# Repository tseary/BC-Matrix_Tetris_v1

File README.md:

# BC-Matrix_Tetris_v1
An Arduino tetris game for the Boldport Club Matrix

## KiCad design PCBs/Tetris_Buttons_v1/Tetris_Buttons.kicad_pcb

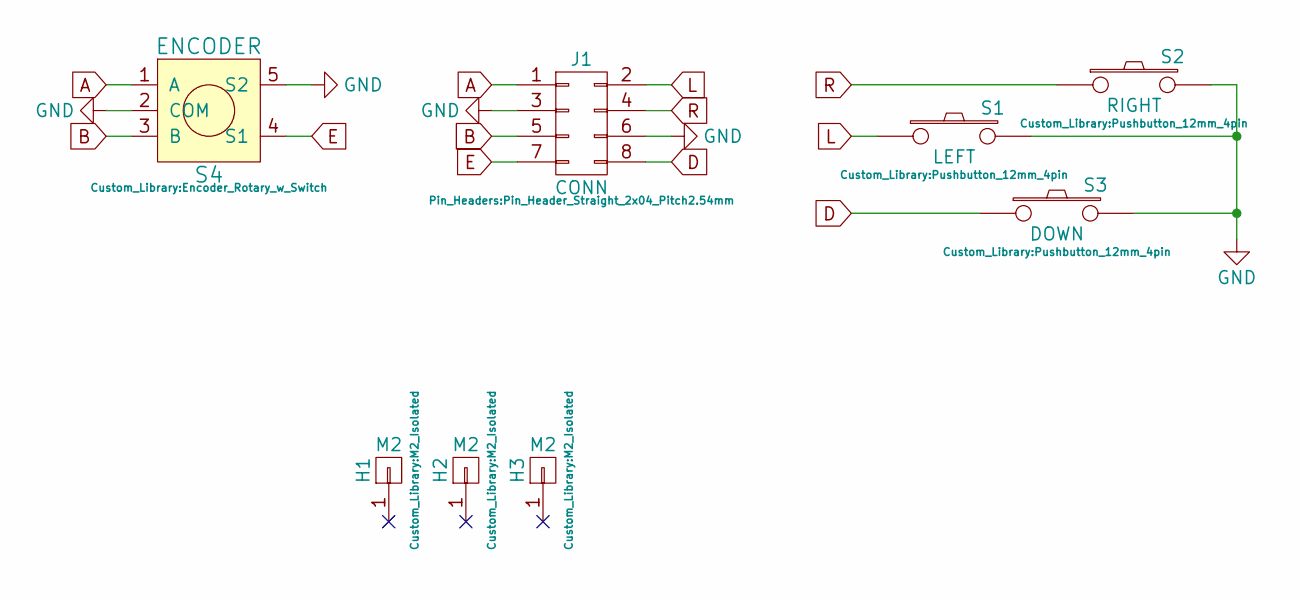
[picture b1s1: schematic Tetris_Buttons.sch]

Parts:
H1, H2, H3: M2; M2_Isolated
J1: CONN; Pin_Header_Straight_2x04_Pitch2.54mm
S1: LEFT; Pushbutton_12mm_4pin
S2: RIGHT; Pushbutton_12mm_4pin
S3: DOWN; Pushbutton_12mm_4pin
S4: ENCODER; Encoder_Rotary_w_Switch

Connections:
A: J1.1, S4.1 (A)
B: J1.5, S4.3 (B)
D: J1.8, S3.1
E: J1.7, S4.4 (S1)
GND: J1.3, J1.6, S1.2, S2.2, S3.2, S4.2 (COM), S4.5 (S2)
L: J1.2, S1.1
R: J1.4, S2.1

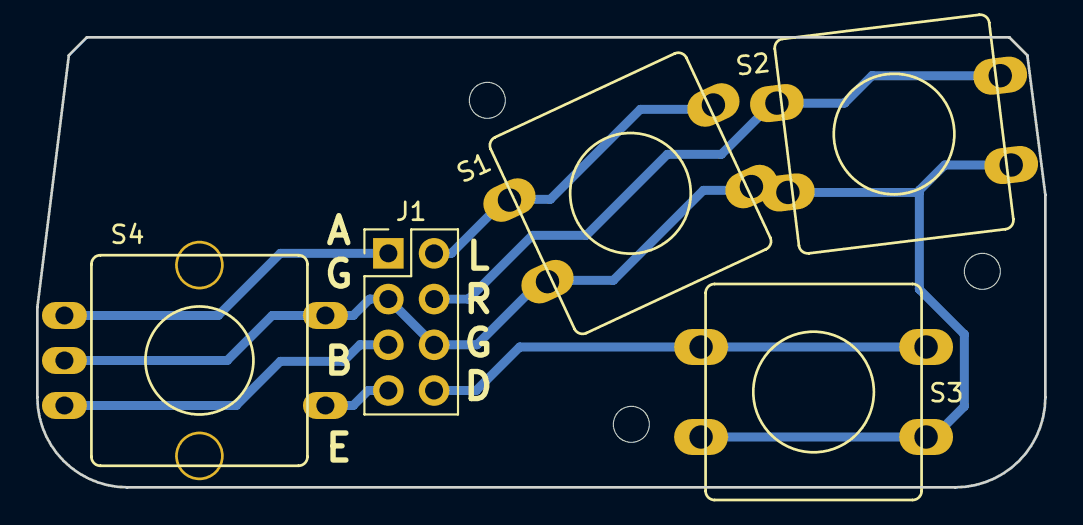
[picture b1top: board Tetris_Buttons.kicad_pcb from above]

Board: 2 copper layers, 56.0 x 25.0 mm, 8 parts (0 on the bottom side), 7 nets.

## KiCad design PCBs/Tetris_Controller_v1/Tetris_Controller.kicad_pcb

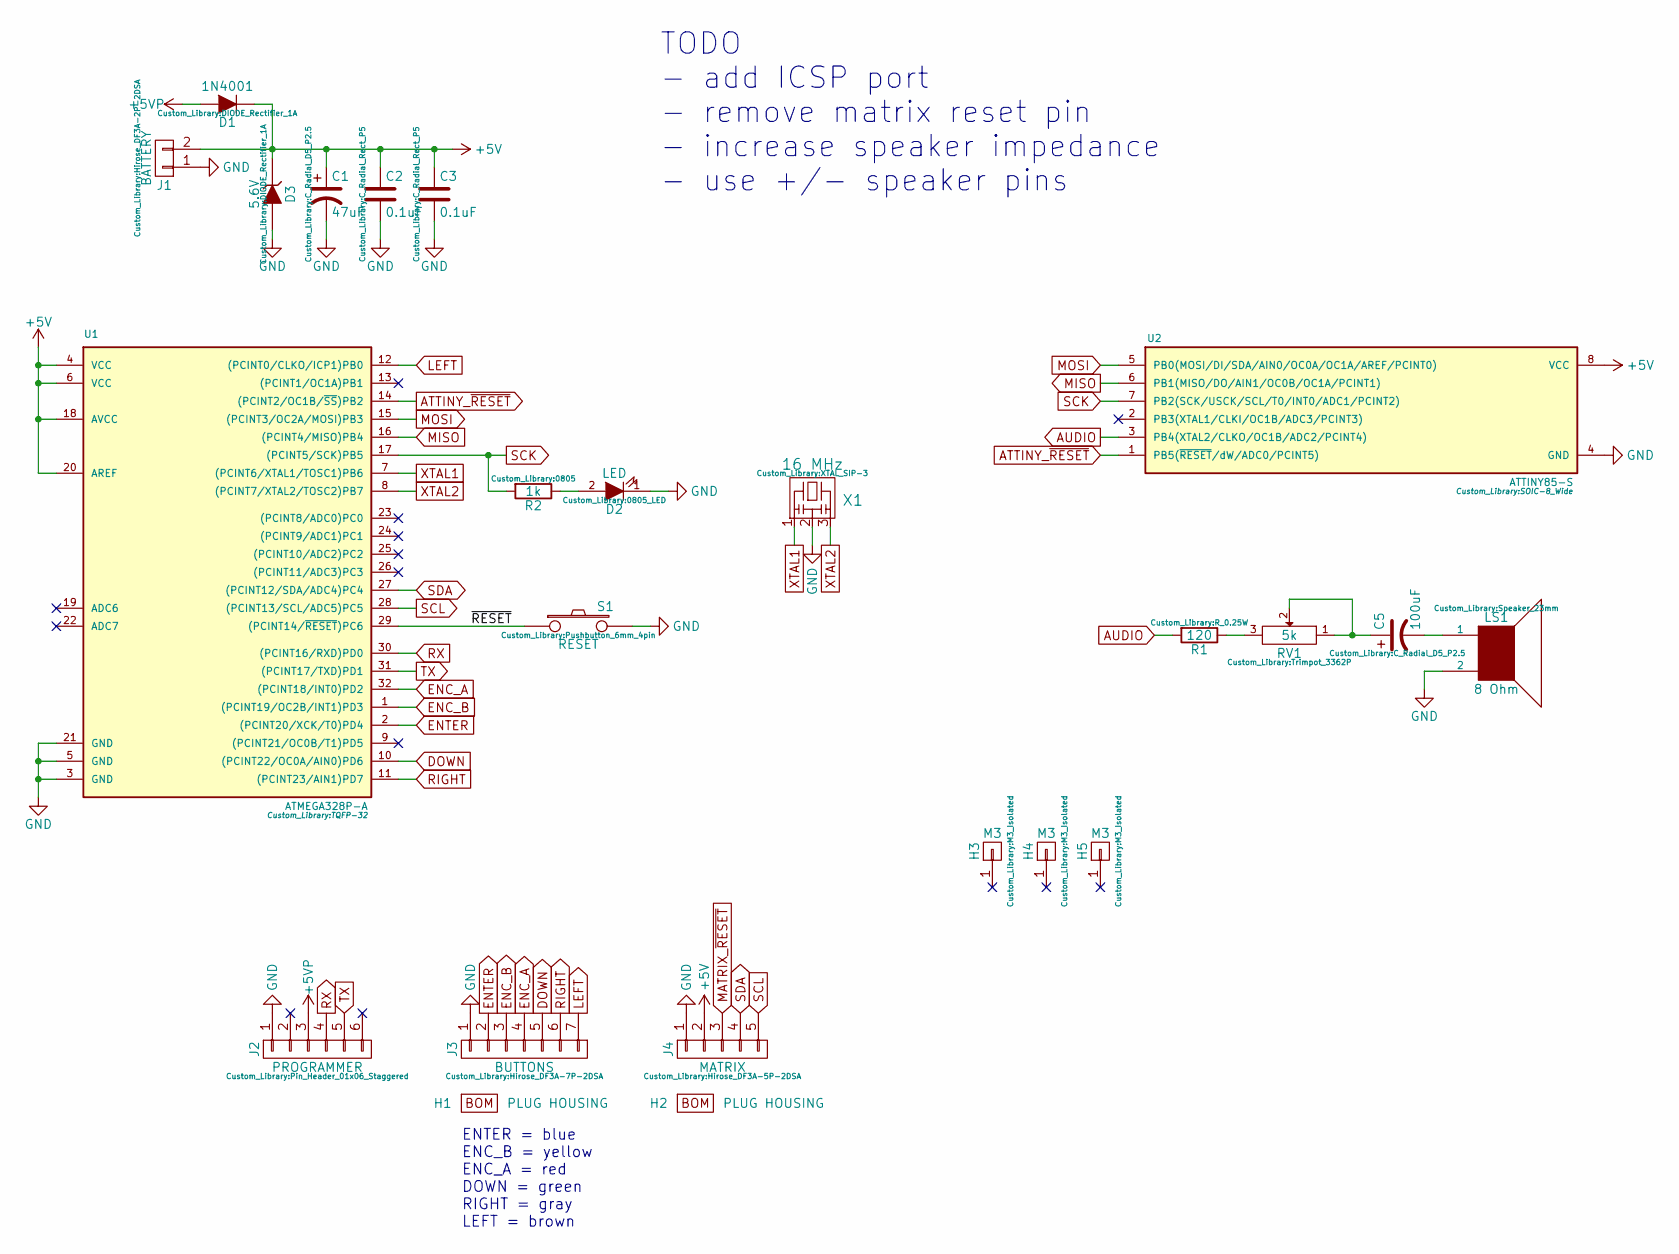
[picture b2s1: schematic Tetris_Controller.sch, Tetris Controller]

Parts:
C1: 47uF; C_Radial_D5_P2.5
C2, C3: 0.1uF; C_Radial_Rect_P5
C5: 100uF; C_Radial_D5_P2.5
D1: 1N4001; DIODE_Rectifier_1A
D2: LED; 0805_LED
D3: 5.6V; DIODE_Rectifier_1A
H1, H2: PLUG HOUSING
H3, H4, H5: M3; M3_Isolated
J1: BATTERY; Hirose_DF3A-2P-2DSA
J2: PROGRAMMER; Pin_Header_01x06_Staggered
J3: BUTTONS; Hirose_DF3A-7P-2DSA
J4: MATRIX; Hirose_DF3A-5P-2DSA
LS1: 8 Ohm; Speaker_23mm
R1: 120; R_0.25W
R2: 1k; 0805
RV1: 5k; Trimpot_3362P
S1: RESET; Pushbutton_6mm_4pin
U1: ATMEGA328P-A; TQFP-32
U2: ATTINY85-S; SOIC-8_Wide
X1: 16 MHz; XTAL_SIP-3

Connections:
+5V: C1.1, C2.1, C3.1, D1.1 (K), D3.1 (K), J1.2, J4.2, U1.4 (VCC), U1.6 (VCC), U1.18 (AVCC), U1.20 (AREF), U2.8 (VCC)
+5VP: D1.2 (A), J2.3
/~RESET: S1.1, U1.29 ((PCINT14/~RESET~)PC6)
ATTINY_~RESET: U1.14 ((PCINT2/OC1B/~SS~)PB2), U2.1 (PB5(~RESET~/dW/ADC0/PCINT5))
AUDIO: R1.2, U2.3 (PB4(XTAL2/CLKO/OC1B/ADC2/PCINT4))
DOWN: J3.5, U1.10 ((PCINT22/OC0A/AIN0)PD6)
ENC_A: J3.4, U1.32 ((PCINT18/INT0)PD2)
ENC_B: J3.3, U1.1 ((PCINT19/OC2B/INT1)PD3)
ENTER: J3.2, U1.2 ((PCINT20/XCK/T0)PD4)
GND: C1.2, C2.2, C3.2, D2.1 (K), D3.2 (A), J1.1, J2.1, J3.1, J4.1, LS1.2, S1.2, U1.3 (GND), U1.5 (GND), U1.21 (GND), U2.4 (GND), X1.2
LEFT: J3.7, U1.12 ((PCINT0/CLKO/ICP1)PB0)
MATRIX_~RESET: J4.3
MISO: U1.16 ((PCINT4/MISO)PB4), U2.6 (PB1(MISO/DO/AIN1/OC0B/OC1A/PCINT1))
MOSI: U1.15 ((PCINT3/OC2A/MOSI)PB3), U2.5 (PB0(MOSI/DI/SDA/AIN0/OC0A/OC1A/AREF/PCI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)
unnamed: C5.1, RV1.1, RV1.2
unnamed: C5.2, LS1.1
unnamed: D2.2 (A), R2.1
unnamed: R1.1, RV1.3
RIGHT: J3.6, U1.11 ((PCINT23/AIN1)PD7)
RX: J2.4, U1.30 ((PCINT16/RXD)PD0)
SCK: R2.2, U1.17 ((PCINT5/SCK)PB5), U2.7 (PB2(SCK/USCK/SCL/T0/INT0/ADC1/PCINT2))
SCL: J4.5, U1.28 ((PCINT13/SCL/ADC5)PC5)
SDA: J4.4, U1.27 ((PCINT12/SDA/ADC4)PC4)
TX: J2.5, U1.31 ((PCINT17/TXD)PD1)
XTAL1: U1.7 ((PCINT6/XTAL1/TOSC1)PB6), X1.1
XTAL2: U1.8 ((PCINT7/XTAL2/TOSC2)PB7), X1.3

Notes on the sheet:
ENTER = blue ENC_B = yellow ENC_A = red DOWN = green RIGHT = gray LEFT = brown
TODO - add ICSP port - remove matrix reset pin - increase speaker impedance - use +/- speaker pins

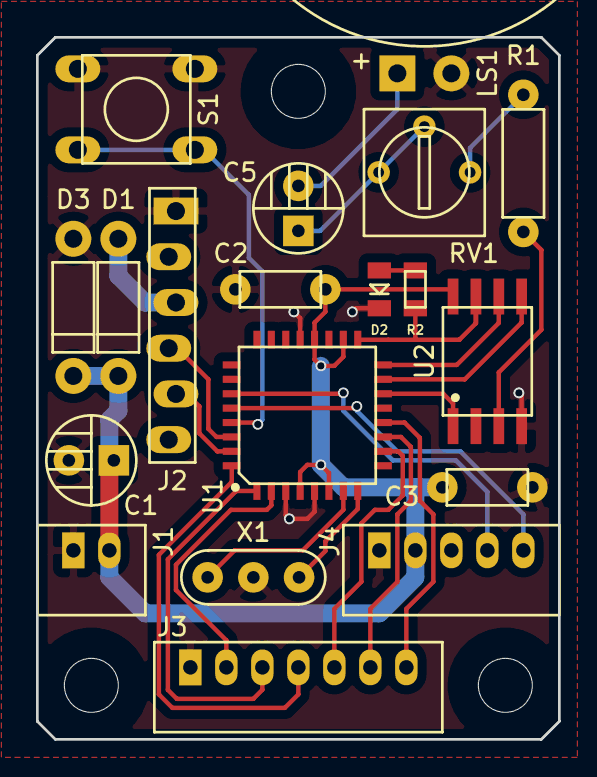
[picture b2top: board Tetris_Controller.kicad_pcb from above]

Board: 2 copper layers, 29.0 x 39.0 mm, 22 parts (0 on the bottom side), 25 nets.

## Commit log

2017-05-29 Initial commit
    Basic game engine, some WIP features.
2017-05-29 Stable
    Fixed curtain animation and minor bugs.
2017-05-30 Added controller circuit documentation.
2017-06-21 Encoder test
    Experimental support for rotary encoder instead of joystick-up to rotate pieces.
2017-06-24 Added music controller program
    Plays the Tetris song in an infinite loop.
2017-06-28 Created Pitch and Value enums
    Separated note pitches from frequencies in Hertz, and values from durations in millis.
2017-06-28 Added SPI pin numbers
2017-06-30 Added untested support for master commands
2017-06-30 Working test of music master control
2017-07-16 Updates for final hardware
    Changed next-level music command from 0x11 to 0x01.
    Changed timing in badTone() to get more accurate frequency.
    Removed nav switch support and replaced with L/R/D/E buttons.
2017-07-20 Main program music integration
    Revised music commands. Added Music.ino (mostly copied from Tetris_Music_Master_Test) to main program and added calls in newGame(), playGame and gameOver().
2017-08-11 EEPROM random seed
    WIP - untested
    Added persistent random seed in EEPROM for more randomness between power cycles.
    Also added high score fields (unused for now).
2017-08-11 Documentation
    Added descriptions of game board geometry and some functions.
2017-08-14 Flashing high score
    Added flashing high score.
    Fixed backwards 5 in five-wide digits.
2017-08-15 WIP High Scores
    Displays text "HIGH SCORE" when a new high score is acheived. (This is any score > 0 because loading the record from EEPROM is commented out.)
2017-10-20 High Score System
    Finished implementing high score system, including player initials and EEPROM load/save. Finished defining letters5High[][] constants.
    Also added music commands for high score, sound on and sound off (all unused as yet).
2017-12-07 Second unit tweaks
    Added differential speaker drive for music controller.
    Added E+L+R button combo to clear high score at power up.
    Changed brightness for stock red LEDs.
2017-12-07 Power-on mute and brightness
    Fixed invalid COMMAND_SOUND_OFF value.
    Implemented brightness adjustment and EEPROM.
    Added DEBUG_SERIAL define, to toggle serial activity.
    Added compile timestamp.
    Started adding game over music support.
2017-12-07 Multi-track music WIP
2017-12-07 Multi-track music code cleanup
    It compiles now, but is untested.
2017-12-07 Music finished
    Tested and fine-tuned music functions for game over and high score.
    Changed game over sound to ascending minor scale.
    Added track change check in badToneDifferential() to allow breaking mid-note.
2017-12-08 Release
    Fixed encoder math that caused dead spot at zero.
    Turned off debug serial.
2018-03-03 Multi-colour brightness correction
    Implemented partial screen dimming for a display with mixed LEDs.
2018-06-21 Tweaks
    Delay before sending first music command.
    Debug output of encoder reading.
2019-09-02 Create Visual Micro project
    Implemented visual micro project.
    Added screen row dimming from EEPROM.
2019-09-03 Fixed push-off
2019-09-03 Push-off cleanup
    Removed serial output for rotating pieces.
    Changed byte to uint8_t.
2019-09-03 Fixed top garbage
    Removed setting tetramino type to "none" in gameOver(). Attempting to draw invalid tetramino results in garbage on screen.
2019-09-03 Rudimentary pause
    Game pauses/unpauses when E button is clicked. Music does not pause yet. Screen freezes during pause.
2019-09-03 Updated TetrisMusic to Visual Micro
2019-09-04 Stop music when paused
    Implemented PAUSE and UNPAUSE commands in music controller.
2019-09-04 Fixed music restart on level up
2019-09-05 Fixed Game Over sound when sound is turned on
2019-09-05 Switch debounce
    Added 100 us delay in game loop to debounce switches. Tested at level 13 to ensure responsiveness.
2019-09-05 Tweaks
    Can now unpause with any input - not just encoder button.
    Moved debounce delay out of main file into Control.ino.
2019-09-05 Low power pause
    Added low power delay during pause and brightness adjustment. Reduced display current while paused.
2019-09-05 Music low power
    Added low-power sleep for music processor when sound is off (or silenced), but not when paused.
2019-09-06 Music reset
    Reset the music controller at power on, to ensure no spurious sounds are played. Also lengthened delay before first music command.
2019-09-07 Comment changes
    Removed obsolete comments describing navigation switch.
2019-12-10 Added KiCad PCBs
    Added the Controller v1 and Buttons v1 KiCad designs. These are provided for reference only and are not recommended for production.
2019-12-13 Change polarity of line brightness
    Changed so that default screen brightness is higher, assuming all EEPROM is set to zero from factory.
2019-12-18 Added support for 3 high scores
    Three high scores are stored and displayed. This update will delete the previous high score.
2019-12-18 Changed EEPROM addresses to preserve screen settings
    This update will not show the old high score, but it also won't be overwritten.
2019-12-18 Added separate high score- and factory-reset codes.
    Made L+D button code do a high score reset, and L+D+R do a factory reset.
    After a factory reset, the game displays "RST" and goes to sleep forever.
2020-01-06 Implemented legacy high score rescue
    If the new high score location contains invalid data, attempt to load from the legacy high score location. This will preserve the old high score when upgrading to the latest firmware.
2020-02-17 Pause counter
    No long pieces if you pause too much.
2020-02-19 Swap tetraminos by pressing L+R
    Added the ability to save and recall tetraminos. One tetramino is stored at a time and can be swapped with the active piece by pressing L and R together.
2020-02-20 Implement swapping (untested)
2020-02-20 Tetramino collision with mask
    Created FIELD_MASK constants. Added optional mask argument to isTetraminoCollision() for deteting collisions only in certain parts of the field.
2020-02-20 Replace rotation collision detection
    Used resolveCollision() when rotating pieces.
2020-02-20 Move L and J off-center
    Moved L and J tetramino center of rotation to allow tucking.
2020-02-20 Reset stored piece
    Clear the stored piece in newGame().
    Moved the center of rotation for J and L tetraminos for even better tucking.
2021-05-12 Increase high score delay
2021-05-12 Reduced curtain density
    Changed fill pattern to 1/3 diagonal stripes to reduce power consumption.
2021-05-13 High score groups
    Implemented separate groups of high scores for swap-piece players and non-swap-piece players.
2021-05-14 EEPROM for sound settings
    Added one byte in EEPROM for sound settings. Now holding the down button while turning on toggles sound rather than turning it off for one game only. This will save battery power for players who typi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
2021-05-14 Minor cleanup
2021-05-14 Inverted sound setting
    Changed the definition of the sound setting in EEPROM so that 0 = sound on. This is the factory default.
2021-05-15 Debounce D button
    Added debounce counter to the D button. The canDropPiece flag is only reset after the D button has been released for 4 consecutive input cycles.
2021-05-15 Added clear bonus
    The player now scores double points for any piece that clears the board.
2021-06-17 Usage metrics counters
    Implemented counters, but no way to read them out yet.
2021-06-18 Serial interface
    Added serial interface to print out usage metrics. Created updateControlAndUsage() for tidiness.
2021-06-19 Reset usage metrics
    Added startup button combination (L+D+E) to reset usage metrics EEPROM.
2021-06-20 Pause text
    Hide the board and display the text "PAUSE" while paused. Added separate picture for special text, and removed blank picture.
2021-06-20 More usage stats
    Added total games and total Tetris's usage metrics.
2021-06-23 Fix numbers not displayed
    Moved some text drawing functions to Display.ino. Added missing drawBoard() call in drawNumber().
